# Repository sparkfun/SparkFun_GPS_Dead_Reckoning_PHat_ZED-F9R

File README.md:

SparkFun GPS-RTK Dead Reckoning pHAT (ZED-F9R) for Raspberry Pi
========================================

[*SparkFun GPS-RTK Dead Reckoning pHAT (ZED-F9R) for Raspberry Pi (GPS-21305)*](https://www.sparkfun.com/products/21305)

The SparkFun ZED-F9R GPS pHAT is a high precision, sensor fusion GPS board with equally impressive configuration options and takes advantage of u-blox's Automotive Dead Reckoning (ADR) technology. The ZED-F9R module provides a highly accurate and continuous position by fusing a 3D IMU sensor, wheel ticks, a vehicle dynamics model, correction data, and GNSS measurements.

The ZED-F9R module is an 184-channel u-blox F9 engine GNSS receiver, meaning it can receive signals from the GPS, GLONASS, Galileo, and BeiDou constellations with ~0.01-meter accuracy! That's right, such accuracy can be achieved with an RTK navigation solution when used with a correction source. Note that the ZED-F9R can only operate as a rover, so you will need to connect to a base station. The module supports the concurrent reception of four GNSS systems. The combination of GNSS and integrated 3D sensor measurements on the ZED-F9R provides accurate, real-time positioning rates of up to 30Hz.

This pHAT maximizes position accuracy in dense cities or covered areas compared to other GPS modules. Even under poor signal conditions, continuous positioning is provided in urban environments and available during complete signal loss (e.g., short tunnels and parking garages). The ZED-F9R is the ultimate solution for autonomous robotic applications that require accurate positioning under challenging conditions.

This u-blox receiver supports a few serial protocols. By default, we used the Raspberry Pi's serial UART to communicate with the module. With pre-soldered headers, no soldering is required to stack the pHAT on a Raspberry Pi, NVIDIA Jetson Nano, Google Coral, or any single-board computer with the 2x20 form factor. We have also broken out a few 0.1"-spaced pins from the u-blox receiver. A Qwiic connector is also added if you need to connect a Qwiic-enabled device.

U-blox-based GPS products are configurable using the popular but dense Windows program u-center. Many different functions can be configured on the ZED-F9R: baud rates, update rates, geofencing, spoofing detection, external interrupts, SBAS/D-GPS, etc.

The SparkFun ZED-F9R GPS pHAT also has an onboard rechargeable battery that provides power to the RTC on the ZED-F9R. This reduces the time-to-first fix from a cold start (~24s) to a hot start (~2s). The battery will maintain RTC and GNSS orbit data without being connected to power for plenty of time.

Repository Contents
-------------------

* **/Documentation** - Data sheets, additional product information
* **/Hardware** - Eagle design files (.brd, .sch)
* **/Production** - Production panel files (.brd)

Documentation
--------------
* **[Library](https://github.com/sparkfun/Qwiic_Ublox_Gps_Py)** - Python library for the ZED-F9R.
* **[Hookup Guide](https://learn.sparkfun.com/tutorials/1172)** - Basic hookup guide for the ZED-F9R.

Product Versions
----------------
* [GPS-21305](https://www.sparkfun.com/products/21305)
* [GPS-16475](https://www.sparkfun.com/products/16475)

Version History
---------------
* [v1.1](https://github.com/sparkfun/SparkFun_GPS_Dead_Reckoning_PHat_ZED-F9R/releases/tag/v1.1)
* [v1.0](https://github.com/sparkfun/SparkFun_GPS_Dead_Reckoning_PHat_ZED-F9R/releases/tag/v1.0) - Initial Release

License Information
-------------------

This product is _**open source**_! 

Please review the LICENSE.md file for license information. 

If you have any questions or concerns on licensing, please contact technical support on our [SparkFun forums](https://forum.sparkfun.com/viewforum.php?f=152).

Distributed as-is; no warranty is given.

- Your friends at SparkFun.

_<COLLABORATION CREDIT>_

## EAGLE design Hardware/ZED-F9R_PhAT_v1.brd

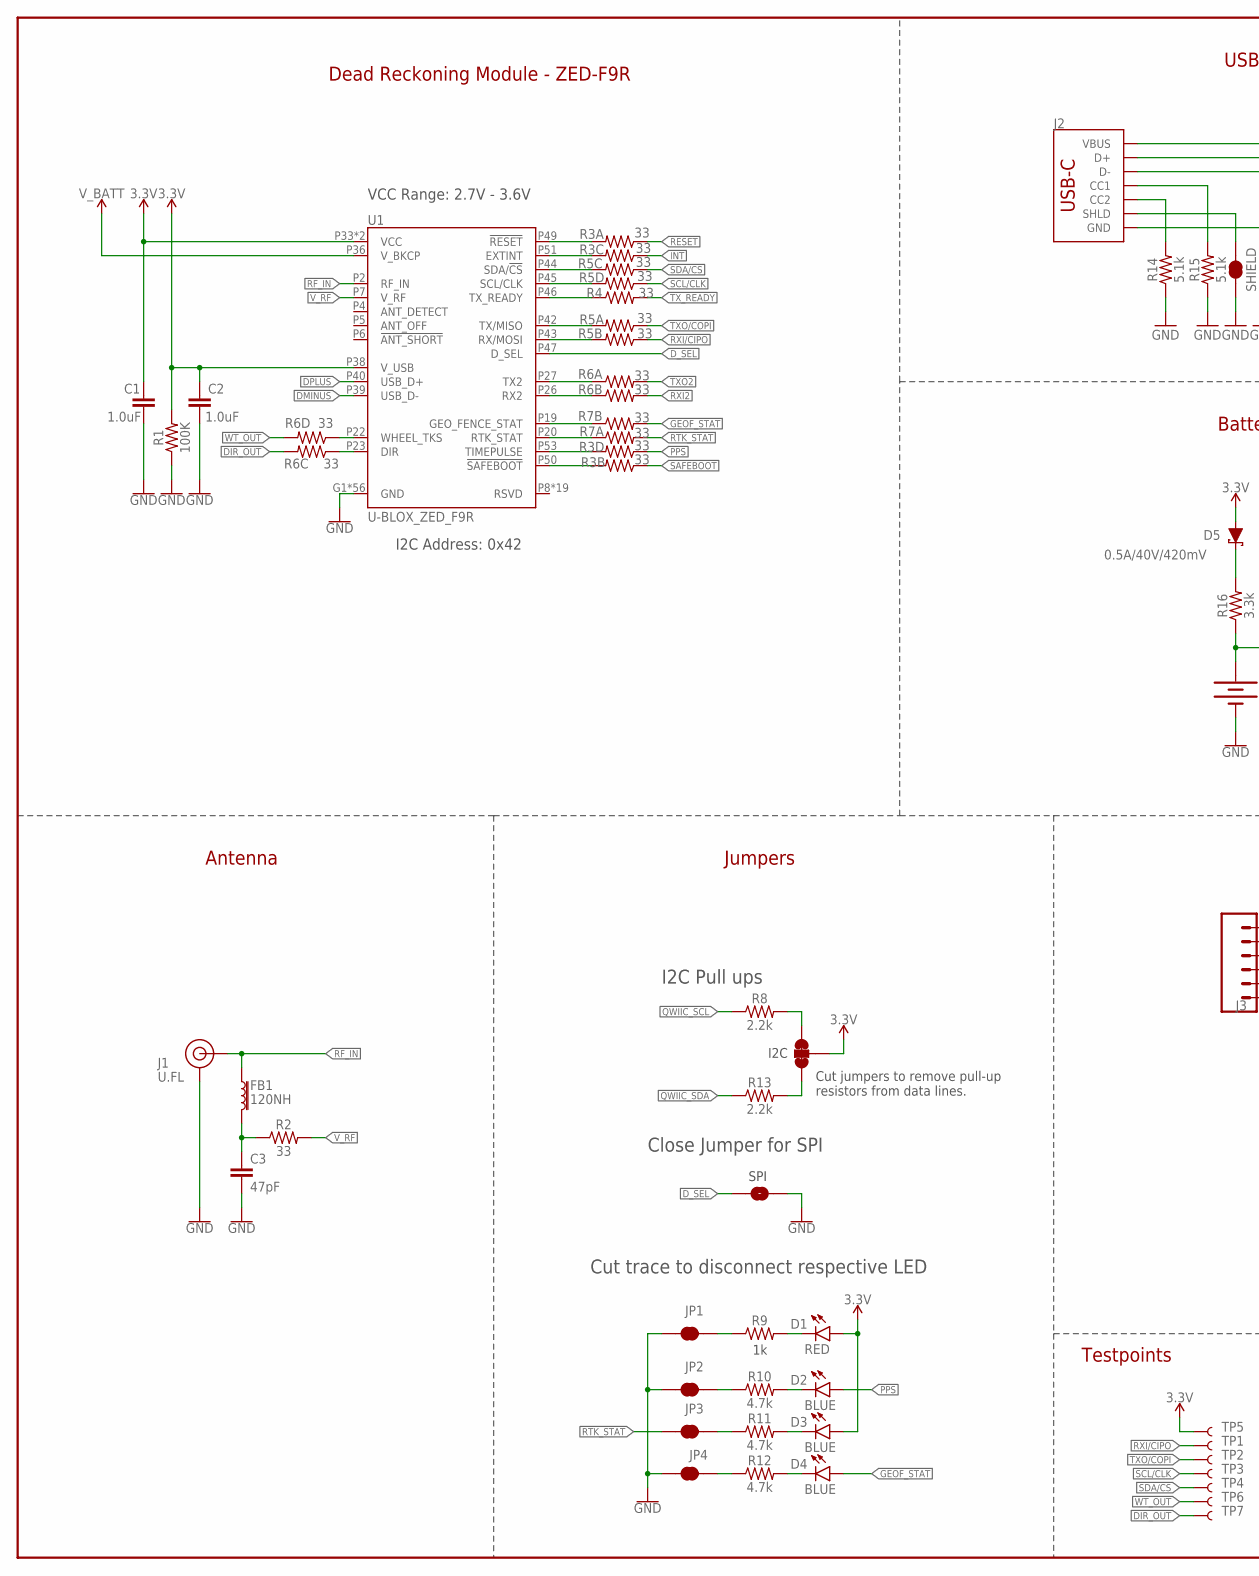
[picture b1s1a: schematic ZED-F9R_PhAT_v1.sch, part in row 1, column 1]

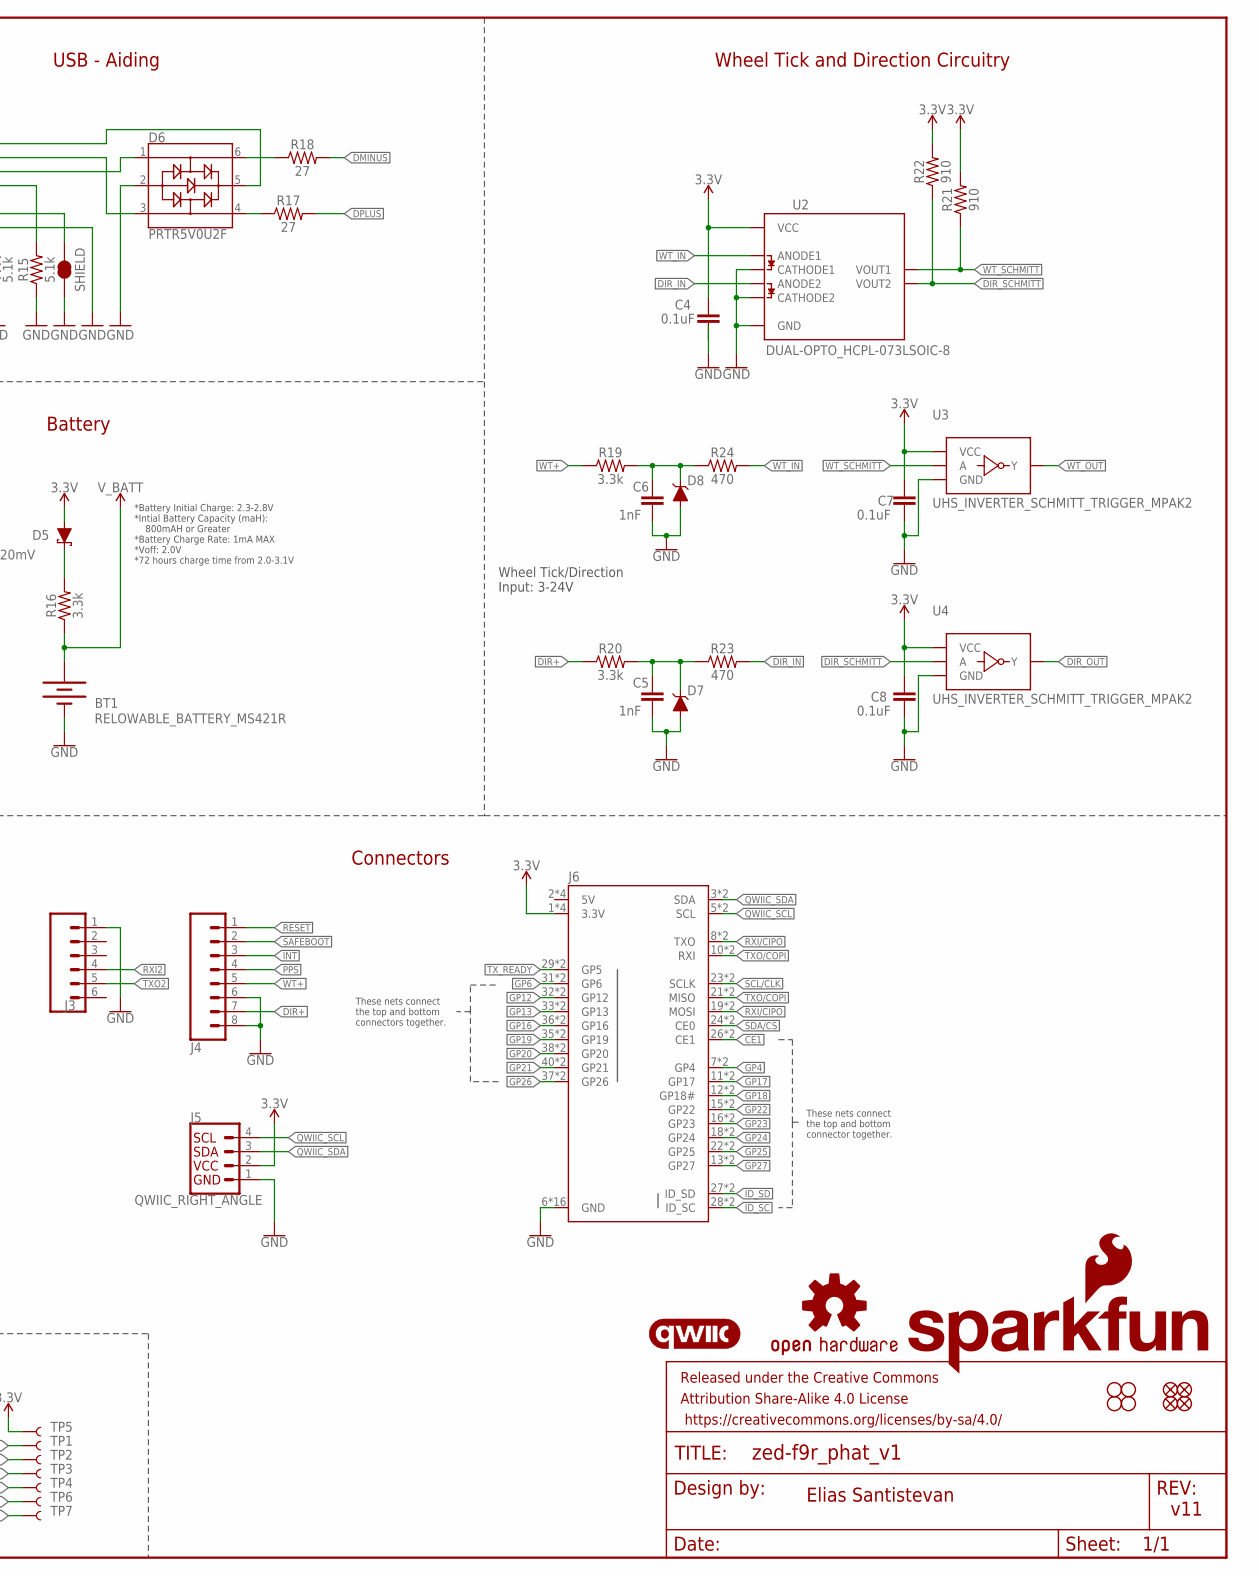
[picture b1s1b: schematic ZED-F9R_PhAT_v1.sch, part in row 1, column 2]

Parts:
BT1: RELOWABLE_BATTERY_MS421R; MS421R_IV03E
C1, C2: 1.0uF; 0402
C3: 47pF; 0402
C4, C7, C8: 0.1uF; 0402
C5, C6: 1nF; 0402
D1: RED; LED-0603
D2, D3, D4: BLUE; LED-0603
D5: 0.5A/40V/420mV; SOD-323
D6: PRTR5V0U2F; SOT886
D7, D8: 15V; SOT23-3
FB1: 120NH; 0402_MURATA
FD1, FD2, FD3, FD4: FIDUCIALUFIDUCIAL; FIDUCIAL-MICRO
FRAME1: FRAME-LEDGER; CREATIVE_COMMONS
H1, H2, H3, H4: STAND-OFFTIGHT; STAND-OFF-TIGHT
J1: U.FL
J2: USB_C_2-LAYER; USB-C-16P
J3: CONN_06NO_SILK_NO_POP; 1X06_NO_SILK
J4: CONN_08NO_SILK_FEMALE_PTH; 1X08_NO_SILK
J5: QWIIC_RIGHT_ANGLE; JST04_1MM_RA
J6: RASPBERRYPI-40-PIN-GPIO_SMD_STACK_NOHOLES_NOREF; RASPBERRY_PI_HAT_40_PIN_SMD_STACKABLE_NOHOLES_NOREF
JP1, JP2, JP3, JP4: JUMPER-SMT_2_NC_TRACE_SILK; SMT-JUMPER_2_NC_TRACE_SILK
JP5: JUMPER-SMT_2_NO_SILK; SMT-JUMPER_2_NO_SILK
JP6: JUMPER-SMT_3_2-NC_TRACE_SILK; SMT-JUMPER_3_2-NC_TRACE_SILK
LOGO1: QWIIC_LOGO_5MM; QWIIC_5MM
LOGO2: OSHW-LOGOM; OSHW-LOGO-M
LOGO3: SFE_LOGO_NAME_FLAME.2_INCH; SFE_LOGO_NAME_FLAME_.2
R1: 100K; 0402
R2, R4: 33; 0603
R3, R5, R6, R7: 33; 1206_RA
R8, R13: 2.2k; 0603
R9: 1k; 0603
R10, R11, R12: 4.7k; 0603
R14, R15: 5.1k; 0402
R16, R19, R20: 3.3k; 0603
R17, R18: 27; 0603
R21, R22: 910; 0603
R23, R24: 470; 0603
SHIELD: JUMPER-SMT_2_NC_TRACE_SILK; SMT-JUMPER_2_NC_TRACE_SILK
TP1, TP2, TP3, TP4, TP5, TP6, TP7: TEST-POINT3X4; PAD.03X.04
U1: U-BLOX_ZED_F9R; UBLOX_ZED_F9R
U2: DUAL-OPTO_HCPL-073LSOIC-8; SO08
U3, U4: UHS_INVERTER_SCHMITT_TRIGGER_MPAK2; SIP6_MICROPAK2

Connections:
3.3V: C1.1, C2.1, C4.1, C7.1, C8.1, D1.A, D3.A, D5.A, J5.2, J6.1 (3.3V), J6.1B (3.3V), J6.17 (3.3V), J6.17B (3.3V), JP6.2, R1.2, R21.2, R22.2, TP5.P$1, U1.P33 (VCC), U1.P34 (VCC), U1.P38 (V_USB), U2.8 (VCC), U3.P6 (VCC), U4.P6 (VCC); also elsewhere on the board
5V: J6.2 (5V), J6.2B (5V), J6.4 (5V), J6.4B (5V)
!RESET: J4.1, R3.P1 (1)
!SAFEBOOT: J4.2, R3.P2 (1)
CE1: J6.26 (CE1), J6.26B (CE1)
DIR+: J4.7, R20.1
DIR_IN: R23.2, U2.4 (ANODE2)
DIR_OUT: R6.P6 (2), TP7.P$1, U4.P4 (Y)
DIR_SCHMITT: R22.1, U2.6 (VOUT2), U4.P2 (A)
DMINUS: R18.2, U1.P39 (USB_D-)
DPLUS: R17.2, U1.P40 (USB_D+)
D_SEL: JP5.1, U1.P47 (D_SEL)
GEOF_STAT: D4.A, R7.P7 (2)
GND: BT1.-, C1.2, C2.2, C3.2, C4.2, C5.2, C6.2, C7.2, C8.2, D6.2, D7.1 (A), D8.1 (A), J1.1 (GND), J1.2 (GND), J2.GND, J2.GND2 (GND), J3.1, J4.6, J4.8, J5.1, J6.6 (GND), J6.6B (GND), J6.9 (GND), J6.9B (GND), J6.14 (GND), J6.14B (GND), J6.20 (GND), J6.20B (GND), J6.25 (GND), J6.25B (GND), J6.30 (GND), J6.30B (GND), J6.34 (GND), J6.34B (GND), J6.39 (GND), J6.39B (GND), JP1.1, JP2.1, JP4.1, JP5.2, R1.1, R14.1, R15.1, SHIELD.1, U1.G1 (GND), U1.G2 (GND), U1.G3 (GND), U1.G4 (GND), U1.G5 (GND), U1.G6 (GND), U1.G7 (GND), U1.G8 (GND), U1.G9 (GND), U1.G10 (GND), U1.G11 (GND), U1.G12 (GND), U1.G13 (GND), U1.G14 (GND), U1.G15 (GND), U1.G16 (GND), U1.G17 (GND), U1.G18 (GND), U1.G19 (GND), U1.G20 (GND), U1.G21 (GND), U1.G22 (GND), U1.G23 (GND), U1.G24 (GND), U1.G25 (GND), U1.G26 (GND), U1.G27 (GND), U1.G28 (GND), U1.G29 (GND), U1.G30 (GND), U1.G31 (GND), U1.G32 (GND), U1.G33 (GND), U1.G34 (GND), U1.G35 (GND), U1.G36 (GND), U1.G37 (GND), U1.G38 (GND), U1.G39 (GND), U1.G40 (GND), U1.G41 (GND), U1.G42 (GND), U1.G43 (GND), U1.G44 (GND), U1.G45 (GND), U1.G46 (GND), U1.G47 (GND), U1.G48 (GND), U1.P1 (GND), U1.P3 (GND), U1.P12 (GND), U1.P14 (GND), U1.P32 (GND), U1.P37 (GND), U1.P41 (GND), U1.P48 (GND), U2.2 (CATHODE1), U2.3 (CATHODE2), U2.5 (GND), U3.P3 (GND), U4.P3 (GND); also elsewhere on the board
GP4: J6.7 (GP4), J6.7B (GP4)
GP6: J6.31 (GP6), J6.31B (GP6)
GP12: J6.32 (GP12), J6.32B (GP12)
GP13: J6.33 (GP13), J6.33B (GP13)
GP16: J6.36 (GP16), J6.36B (GP16)
GP17: J6.11 (GP17), J6.11B (GP17)
GP18: J6.12 (GP18#), J6.12B (GP18#)
GP19: J6.35 (GP19), J6.35B (GP19)
GP20: J6.38 (GP20), J6.38B (GP20)
GP21: J6.40 (GP21), J6.40B (GP21)
GP22: J6.15 (GP22), J6.15B (GP22)
GP23: J6.16 (GP23), J6.16B (GP23)
GP24: J6.18 (GP24), J6.18B (GP24)
GP25: J6.22 (GP25), J6.22B (GP25)
GP26: J6.37 (GP26), J6.37B (GP26)
GP27: J6.13 (GP27), J6.13B (GP27)
ID_SC: J6.28 (ID_SC), J6.28B (ID_SC)
ID_SD: J6.27 (ID_SD), J6.27B (ID_SD)
INT: J4.3, R3.P3 (1)
unnamed: JP6.1, R13.2
unnamed: D5.C, R16.2
unnamed: JP6.3, R8.2
unnamed: D1.C, R9.2
unnamed: C3.1, FB1.P2 (2), R2.1
unnamed: D6.6, R18.1
unnamed: D6.4, R17.1
unnamed: JP1.2, R9.1
unnamed: D6.3, J2.A6 (D+), J2.B6 (D+)
unnamed: D6.5, J2.VBUS1 (VBUS), J2.VBUS2 (VBUS)
unnamed: D6.1, J2.A7 (D-), J2.B7 (D-)
unnamed: J2.B5 (CC2), R14.2
unnamed: R3.P8 (2), U1.P49 (!RESET!)
unnamed: R3.P6 (2), U1.P51 (EXTINT)
unnamed: R5.P6 (2), U1.P44 (SDA/!CS!)
unnamed: JP4.2, R12.1
unnamed: D4.C, R12.2
unnamed: J2.A5 (CC1), R15.2
unnamed: R5.P5 (2), U1.P45 (SCL/CLK)
unnamed: R4.1, U1.P46 (TX_READY)
unnamed: R5.P8 (2), U1.P42 (TX/MISO)
unnamed: JP3.2, R11.1
unnamed: JP2.2, R10.1
unnamed: D2.C, R10.2
unnamed: D3.C, R11.2
unnamed: R5.P7 (2), U1.P43 (RX/MOSI)
unnamed: C6.1, D8.3 (C), R19.2, R24.1
unnamed: R7.P2 (1), U1.P19 (GEO_FENCE_STAT)
unnamed: R7.P1 (1), U1.P20 (RTK_STAT)
unnamed: R3.P5 (2), U1.P53 (TIMEPULSE)
unnamed: R3.P7 (2), U1.P50 (!SAFEBOOT!)
unnamed: R6.P1 (1), U1.P27 (TX2)
unnamed: R6.P2 (1), U1.P26 (RX2)
unnamed: R6.P4 (1), U1.P22 (WHEEL_TKS)
unnamed: R6.P3 (1), U1.P23 (DIR)
unnamed: C5.1, D7.3 (C), R20.2, R23.1
PPS: D2.A, J4.4, R3.P4 (1)
QWIIC_SCL: J5.4, J6.5 (SCL), J6.5B (SCL), R8.1
QWIIC_SDA: J5.3, J6.3 (SDA), J6.3B (SDA), R13.1
RF_IN: FB1.P1 (1), J1.FEED (SIGNAL), U1.P2 (RF_IN)
RTK_STAT: JP3.1, R7.P8 (2)
RXI2: J3.4, R6.P7 (2)
RXI/CIPO: J6.8 (TXO), J6.8B (TXO), J6.19 (MOSI), J6.19B (MOSI), R5.P2 (1), TP1.P$1
SCL/CLK: J6.23 (SCLK), J6.23B (SCLK), R5.P4 (1), TP3.P$1
SDA/!CS: J6.24 (CE0), J6.24B (CE0), R5.P3 (1), TP4.P$1
SHIELD: J2.SHLD1 (SHLD), J2.SHLD2 (SHLD), J2.SHLD3 (SHLD), J2.SHLD4 (SHLD), SHIELD.2
TXO2: J3.5, R6.P8 (2)
TXO/COPI: J6.10 (RXI), J6.10B (RXI), J6.21 (MISO), J6.21B (MISO), R5.P1 (1), TP2.P$1
TX_READY: J6.29 (GP5), J6.29B (GP5), R4.2
V_BATT: BT1.+, R16.1, U1.P36 (V_BKCP); also elsewhere on the board
V_RF: R2.2, U1.P7 (V_RF)
WT+: J4.5, R19.1
WT_IN: R24.2, U2.1 (ANODE1)
WT_OUT: R6.P5 (2), TP6.P$1, U3.P4 (Y)
WT_SCHMITT: R21.1, U2.7 (VOUT1), U3.P2 (A)

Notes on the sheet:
v11
Elias Santistevan
Dead Reckoning Module - ZED-F9R
Battery
Connectors
Jumpers
Close Jumper for SPI
I2C Pull ups
Cut trace to disconnect respective LED
Antenna
*Battery Initial Charge: 2.3-2.8V *Intial Battery Capacity (maH): 800mAH or Greater *Battery Charge Rate: 1mA MAX *Voff: 2.0V *72 hours charge time from 2.0-3.1V
VCC Range: 2.7V - 3.6V
I2C Address: 0x42
USB - Aiding
Cut jumpers to remove pull-up resistors from data lines.
SPI
I2C
Testpoints
These nets connect the top and bottom connector together.
These nets connect the top and bottom connectors together.
Wheel Tick and Direction Circuitry
Wheel Tick/Direction Input: 3-24V

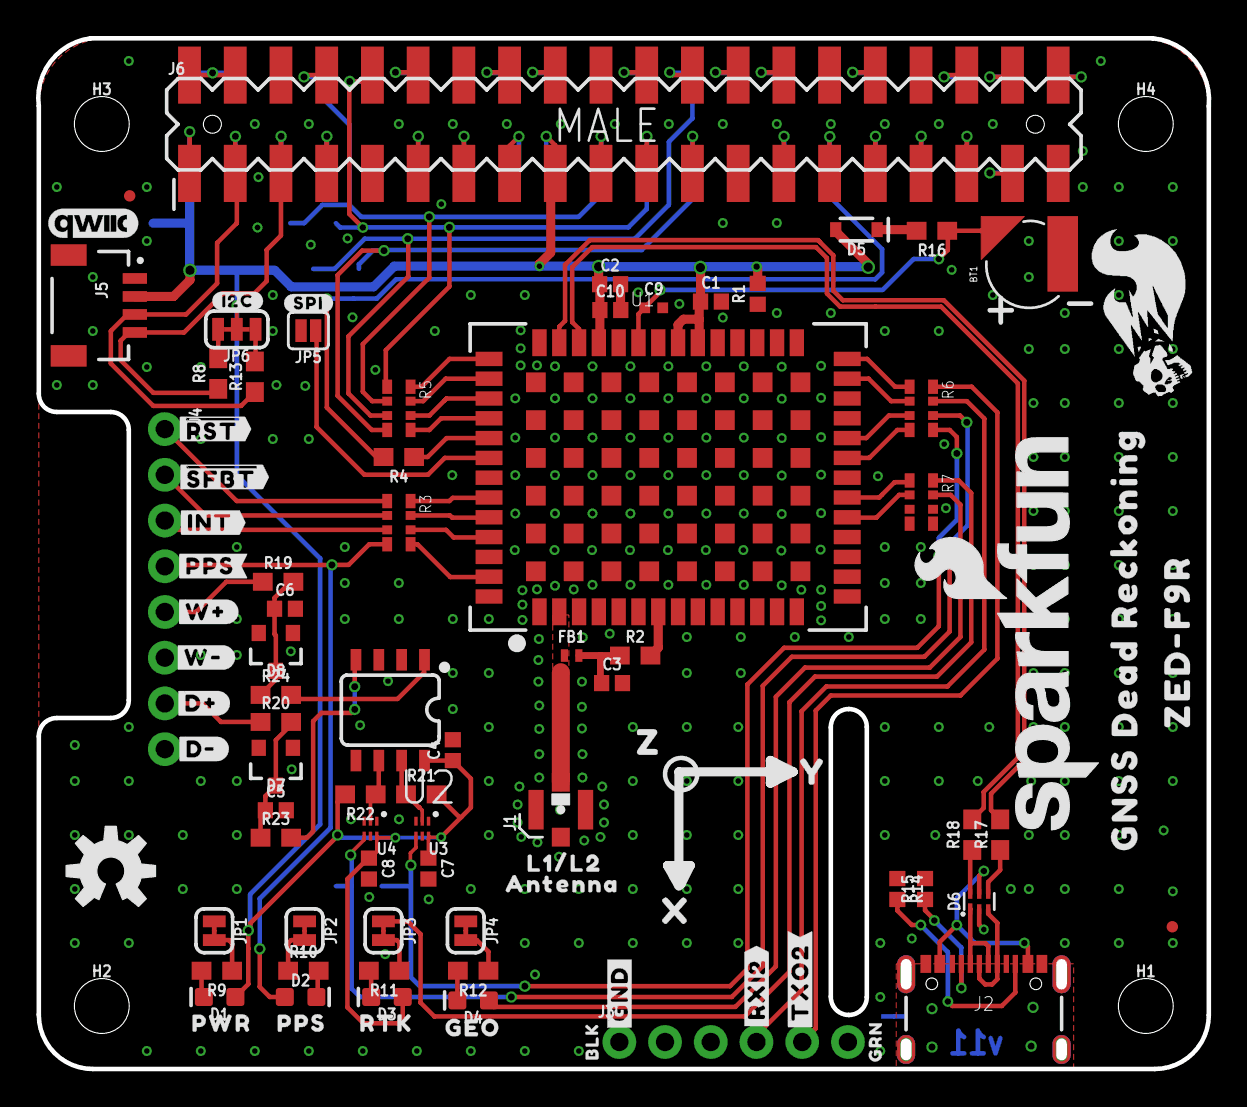
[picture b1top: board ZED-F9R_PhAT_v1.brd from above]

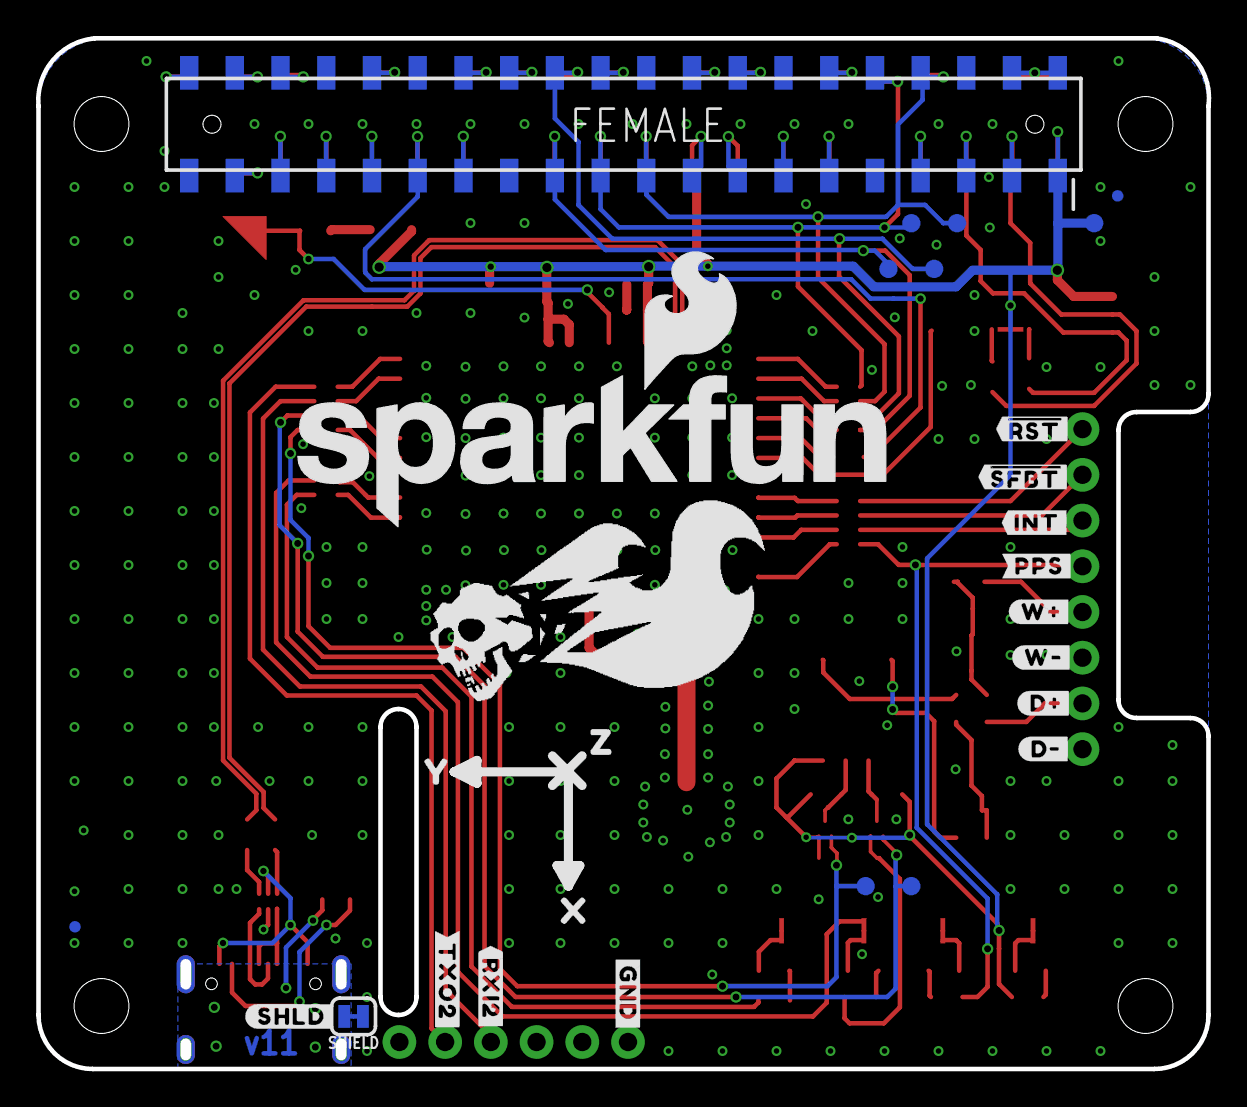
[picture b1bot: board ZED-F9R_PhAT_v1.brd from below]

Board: 2 copper layers, 65.0 x 57.3 mm, 124 parts (27 on the bottom side), 88 nets.

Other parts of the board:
C9: 2.2uF; 0402-TIGHT
C10: 1.0uF; 0402
U$1: ##RST##28
U$2: ##SFBT##30
U$3: PPS9
U$4: PWR7
U$5: GEO11
U$6: #RXI2#34
U$7: #INT#1
U$8: #PPS#3
U$9: SFE_LOGO_NAME_FLAME_.3@1
U$10: #TXO2#235
U$11: #W##2253
U$12: #W##2254
U$13: #D##2249
U$14: GNSS_DEAD_RECKONING25
U$15: #D##2250
U$16: ZED#F9R25
U$17: BLK22
U$18, U$19: #GND#20
U$20: #SPI#4
U$21: L1#L26
U$22: #I2C#5
U$23: RTK13
U$24: GRN23
U$25, U$28: Z20
U$26, U$29: Y19
U$27, U$45: X18
U$31, U$36: DEAD#RECKONING#GPS#BOARD#SILK#FINAL#JPG
U$32: ##RST##27
U$33: ##SFBT##29
U$34: #INT#0
U$35: #PPS#2
U$37: #W##2251
U$38: #W##2252
U$39: #D##2247
U$40: #D##2248
U$41: ANTENNA6
U$42: #TXO2#236
U$43: #RXI2#35
U$44: #SHLD#2258

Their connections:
3.3V: C10.1; also elsewhere on the board
GND: C9.2, C10.2; also elsewhere on the board
V_BATT: C9.1; also elsewhere on the board

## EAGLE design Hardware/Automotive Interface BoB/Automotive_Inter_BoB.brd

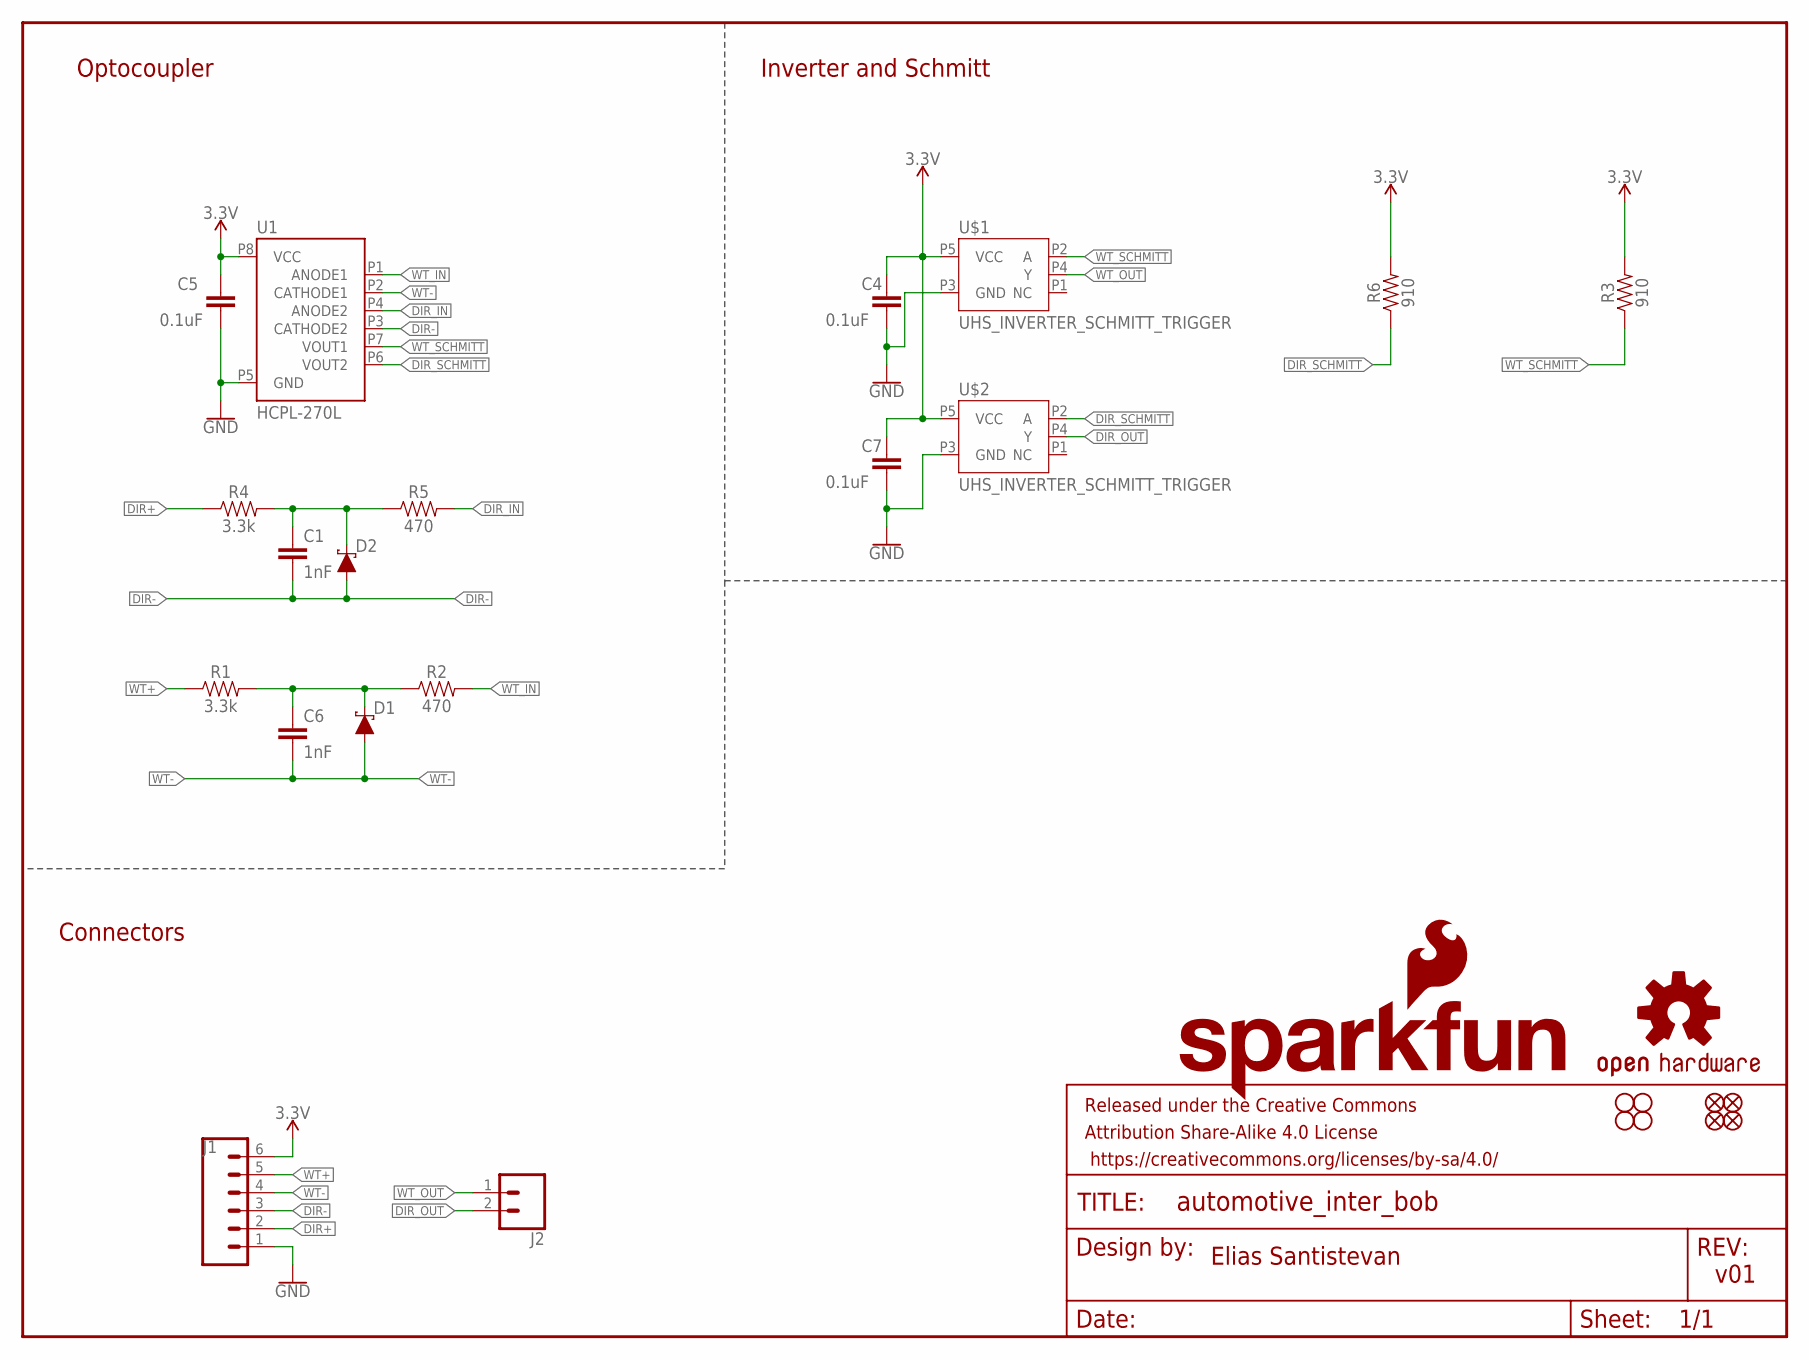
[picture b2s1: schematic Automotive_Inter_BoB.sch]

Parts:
C1, C6: 1nF; 0603
C4, C5, C7: 0.1uF; 0603
D1, D2: 0.5A/40V/420mV; SOD-323
FD1, FD2, FD3, FD4: FIDUCIALUFIDUCIAL; FIDUCIAL-MICRO
FRAME1: FRAME-LETTER; CREATIVE_COMMONS
H1, H2, H3, H4: STAND-OFF
J1: CONN_06NO_SILK_NO_POP; 1X06_NO_SILK
J2: CONN_021X02_NO_SILK; 1X02_NO_SILK
LOGO1: SFE_LOGO_NAME_FLAME.1_INCH; SFE_LOGO_NAME_FLAME_.1
LOGO2: OSHW-LOGOS; OSHW-LOGO-S
R1, R4: 3.3k; 0603
R2, R5: 470; 0603
R3, R6: 910; 0603
U1: HCPL-270L; SOP_8-PIN
U$1, U$2: UHS_INVERTER_SCHMITT_TRIGGER; SC-74A

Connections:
3.3V: C4.1, C5.1, C7.1, J1.6, R3.2, R6.2, U1.P8 (VCC), U$1.P5 (VCC), U$2.P5 (VCC)
DIR+: J1.2, R4.1
DIR-: C1.2, D2.A, J1.3, U1.P3 (CATHODE2)
DIR_IN: R5.2, U1.P4 (ANODE2)
DIR_OUT: J2.2, U$2.P4 (Y)
DIR_SCHMITT: R6.1, U1.P6 (VOUT2), U$2.P2 (A)
GND: C4.2, C5.2, C7.2, J1.1, U1.P5 (GND), U$1.P3 (GND), U$2.P3 (GND)
unnamed: C6.1, D1.C, R1.2, R2.1
unnamed: C1.1, D2.C, R4.2, R5.1
WT+: J1.5, R1.1
WT-: C6.2, D1.A, J1.4, U1.P2 (CATHODE1)
WT_IN: R2.2, U1.P1 (ANODE1)
WT_OUT: J2.1, U$1.P4 (Y)
WT_SCHMITT: R3.1, U1.P7 (VOUT1), U$1.P2 (A)

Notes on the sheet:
Elias Santistevan
v01
Optocoupler
Inverter and Schmitt
Connectors

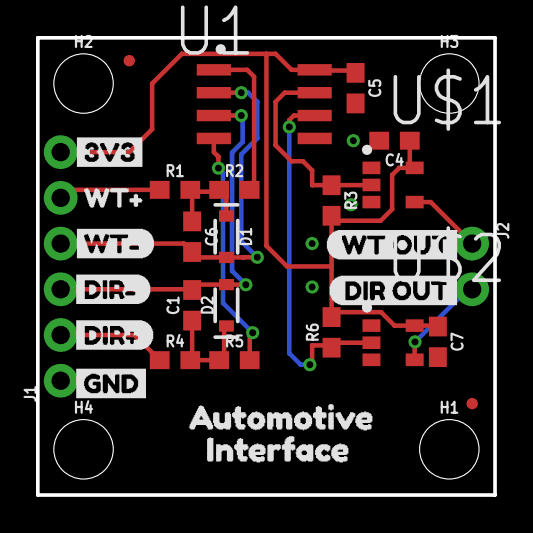
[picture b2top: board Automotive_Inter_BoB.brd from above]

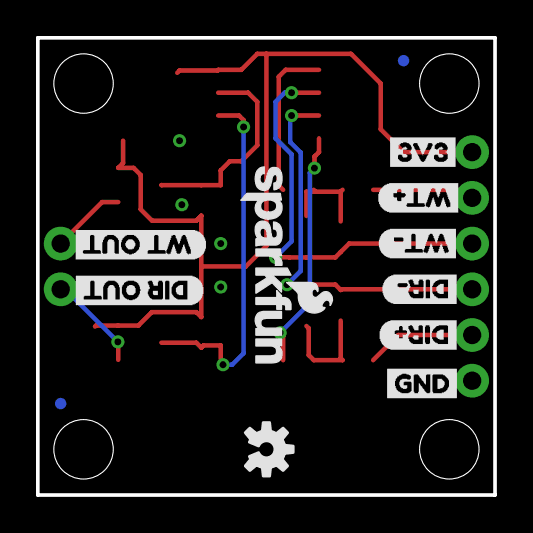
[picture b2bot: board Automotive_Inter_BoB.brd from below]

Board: 2 copper layers, 25.4 x 25.4 mm, 47 parts (12 on the bottom side), 14 nets.

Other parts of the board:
U$3, U$11: DIR#2
U$4, U$12: DIR#3
U$5, U$15: WT#1
U$6, U$14: WT#0
U$7, U$16: WT_OUT4
U$8, U$13: DIR_OUT5
U$9: AUTOMOTIVE6
U$10: INTERFACE7
U$17, U$19: 3V3-04
U$18, U$20: GND-04

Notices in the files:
parts and their libraries:
SparkFun-Aesthetics: Licensing: Creative Commons ShareAlike 4.0 International - https://creativecommons.org/licenses/by-sa/4.0
SparkFun-Aesthetics: Released under the Creative Commons Attribution Share-Alike 4.0 License
SparkFun-Aesthetics: https://creativecommons.org/licenses/by-sa/4.0
